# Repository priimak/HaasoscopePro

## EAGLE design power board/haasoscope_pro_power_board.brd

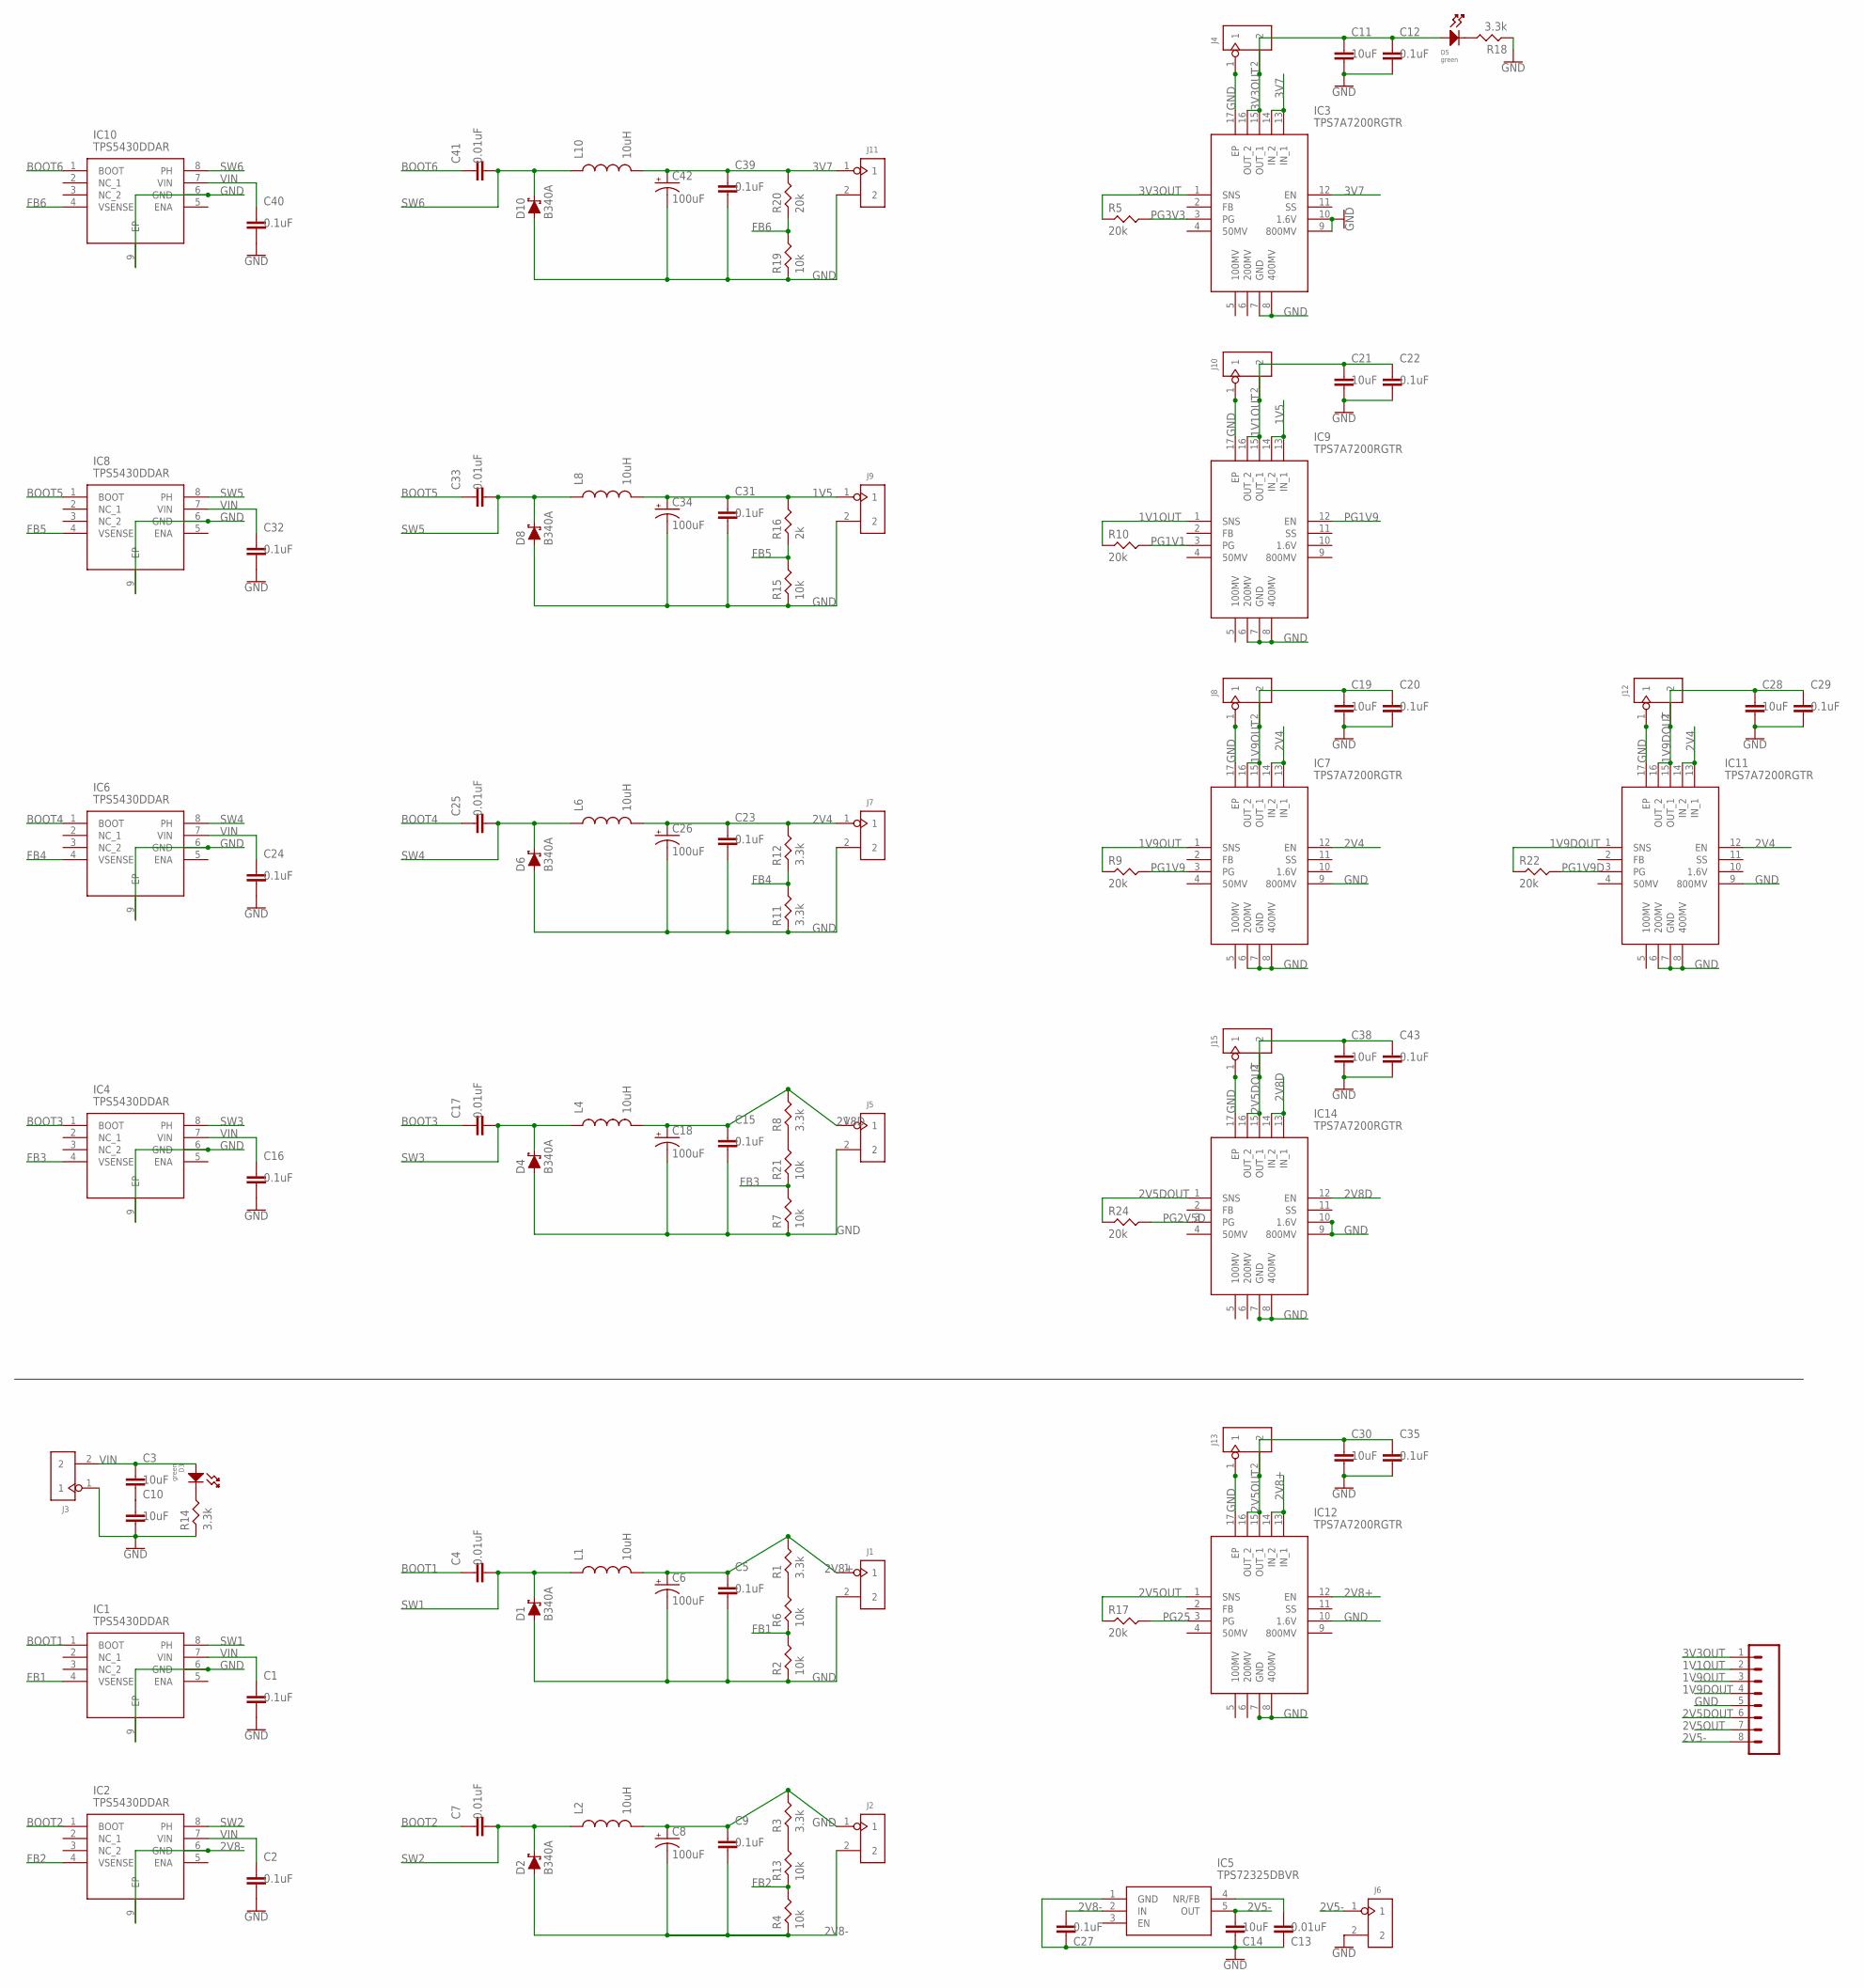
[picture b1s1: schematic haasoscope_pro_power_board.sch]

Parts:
C1, C2, C5, C9, C12, C15, C16, C20, C22, C23, C24, C27, C29, C31, C32, C35, C39, C40, C43: 0.1uF; RESC0402_N
C3, C10, C11, C14, C19, C21, C28, C30, C38: 10uF; RESC0805_N
C4, C7, C13, C17, C25, C33, C41: 0.01uF; RESC0402_N
C6, C8, C18, C26, C34, C42: 100uF; VISHAY_C; LCSC C7230
D1, D2, D4, D6, D8, D10: B340A; SMA-DIODE; LCSC C64982
D3, D5: green; LED0805
IC1, IC2, IC4, IC6, IC8, IC10: TPS5430DDAR; SOIC127P600X170-9N
IC3, IC7, IC9, IC11, IC12, IC14: TPS7A7200RGTR; QFN50P300X300X100-17N
IC5: TPS72325DBVR; SOT95P280X145-5N
J1, J2, J3, J4, J5, J6, J7, J8, J9, J10, J11, J12, J13, J15: 2p-2.54; H2-2.54
J16: 8pin; 1X08
L1, L2, L4, L6, L8, L10: 10uH; CDRH125; LCSC C339970
R1, R3, R8, R11, R12, R14, R18: 3.3k; RES-0402
R2, R4, R6, R7, R13, R15, R19, R21: 10k; RES-0402
R5, R9, R10, R17, R20, R22, R24: 20k; RES-0402
R16: 2k; RES-0402

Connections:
1V1OUT: C21.1, C22.1, IC9.1 (SNS), IC9.15 (OUT_1), IC9.16 (OUT_2), J10.2, J16.2, R10.P$1
1V5: C31.1, C34.+, IC9.13 (IN_1), IC9.14 (IN_2), J9.1, L8.2, R16.P$2
1V9DOUT: C28.1, C29.1, IC11.1 (SNS), IC11.15 (OUT_1), IC11.16 (OUT_2), J12.2, J16.4, R22.P$1
1V9OUT: C19.1, C20.1, IC7.1 (SNS), IC7.15 (OUT_1), IC7.16 (OUT_2), J8.2, J16.3, R9.P$1
2V4: C23.1, C26.+, IC7.12 (EN), IC7.13 (IN_1), IC7.14 (IN_2), IC11.12 (EN), IC11.13 (IN_1), IC11.14 (IN_2), J7.1, L6.2, R12.P$2
2V5-: C14.1, IC5.5 (OUT), J6.1, J16.8
2V5DOUT: C38.1, C43.1, IC14.1 (SNS), IC14.15 (OUT_1), IC14.16 (OUT_2), J15.2, J16.6, R24.P$1
2V5OUT: C30.1, C35.1, IC12.1 (SNS), IC12.15 (OUT_1), IC12.16 (OUT_2), J13.2, J16.7, R17.P$1
2V8+: C5.1, C6.+, IC12.12 (EN), IC12.13 (IN_1), IC12.14 (IN_2), J1.1, L1.2, R1.P$2
2V8-: C8.-, C9.2, C27.1, D2.A, IC2.6 (GND), IC2.9 (EP), IC5.2 (IN), J2.2, R4.P$1
2V8D: C15.1, C18.+, IC14.12 (EN), IC14.13 (IN_1), IC14.14 (IN_2), J5.1, L4.2, R8.P$2
3V3OUT: C11.1, C12.1, D5.ANODE, IC3.1 (SNS), IC3.15 (OUT_1), IC3.16 (OUT_2), J4.2, J16.1, R5.P$1
3V7: C39.1, C42.+, IC3.12 (EN), IC3.13 (IN_1), IC3.14 (IN_2), J11.1, L10.2, R20.P$2
BOOT1: C4.1, IC1.1 (BOOT)
BOOT2: C7.1, IC2.1 (BOOT)
BOOT3: C17.1, IC4.1 (BOOT)
BOOT4: C25.1, IC6.1 (BOOT)
BOOT5: C33.1, IC8.1 (BOOT)
BOOT6: C41.1, IC10.1 (BOOT)
FB1: IC1.4 (VSENSE), R2.P$2, R6.P$1
FB2: IC2.4 (VSENSE), R4.P$2, R13.P$1
FB3: IC4.4 (VSENSE), R7.P$2, R21.P$1
FB4: IC6.4 (VSENSE), R11.P$2, R12.P$1
FB5: IC8.4 (VSENSE), R15.P$2, R16.P$1
FB6: IC10.4 (VSENSE), R19.P$2, R20.P$1
GND: C1.2, C2.2, C5.2, C6.-, C8.+, C9.1, C10.2, C11.2, C12.2, C13.2, C14.2, C15.2, C16.2, C18.-, C19.2, C20.2, C21.2, C22.2, C23.2, C24.2, C26.-, C27.2, C28.2, C29.2, C30.2, C31.2, C32.2, C34.-, C35.2, C38.2, C39.2, C40.2, C42.-, C43.2, D1.A, D4.A, D6.A, D8.A, D10.A, IC1.6 (GND), IC1.9 (EP), IC3.7 (GND), IC3.8 (400MV), IC3.9 (800MV), IC3.10 (1.6V), IC3.17 (EP), IC4.6 (GND), IC4.9 (EP), IC5.1 (GND), IC6.6 (GND), IC6.9 (EP), IC7.6 (200MV), IC7.7 (GND), IC7.8 (400MV), IC7.9 (800MV), IC7.17 (EP), IC8.6 (GND), IC8.9 (EP), IC9.6 (200MV), IC9.7 (GND), IC9.8 (400MV), IC9.17 (EP), IC10.6 (GND), IC10.9 (EP), IC11.6 (200MV), IC11.7 (GND), IC11.8 (400MV), IC11.9 (800MV), IC11.17 (EP), IC12.7 (GND), IC12.8 (400MV), IC12.10 (1.6V), IC12.17 (EP), IC14.7 (GND), IC14.8 (400MV), IC14.9 (800MV), IC14.10 (1.6V), IC14.17 (EP), J1.2, J2.1, J3.1, J4.1, J5.2, J6.2, J7.2, J8.1, J9.2, J10.1, J11.2, J12.1, J13.1, J15.1, J16.5, L2.2, R2.P$1, R3.P$2, R7.P$1, R11.P$1, R14.P$1, R15.P$1, R18.P$1, R19.P$1; also elsewhere on the board
unnamed: R1.P$1, R6.P$2
unnamed: R3.P$1, R13.P$2
unnamed: C3.2, C10.1
unnamed: C13.1, IC5.4 (NR/FB)
unnamed: D3.CATHODE, R14.P$2
unnamed: D5.CATHODE, R18.P$2
unnamed: R8.P$1, R21.P$2
unnamed 33: IC3.5 (100MV); also elsewhere on the board
unnamed 34: IC9.5 (100MV); also elsewhere on the board
unnamed 35: IC7.5 (100MV); also elsewhere on the board
PG1V1: IC9.3 (PG), R10.P$2
PG1V9: IC7.3 (PG), IC9.12 (EN), R9.P$2
PG1V9D: IC11.3 (PG), R22.P$2
PG2V5D: IC14.3 (PG), R24.P$2
PG3V3: IC3.3 (PG), R5.P$2
PG25: IC12.3 (PG), R17.P$2
SW1: C4.2, D1.C, IC1.8 (PH), L1.1
SW2: C7.2, D2.C, IC2.8 (PH), L2.1
SW3: C17.2, D4.C, IC4.8 (PH), L4.1
SW4: C25.2, D6.C, IC6.8 (PH), L6.1
SW5: C33.2, D8.C, IC8.8 (PH), L8.1
SW6: C41.2, D10.C, IC10.8 (PH), L10.1
VIN: C1.1, C2.1, C3.1, C16.1, C24.1, C32.1, C40.1, D3.ANODE, IC1.7 (VIN), IC2.7 (VIN), IC4.7 (VIN), IC6.7 (VIN), IC8.7 (VIN), IC10.7 (VIN), J3.2; also elsewhere on the board

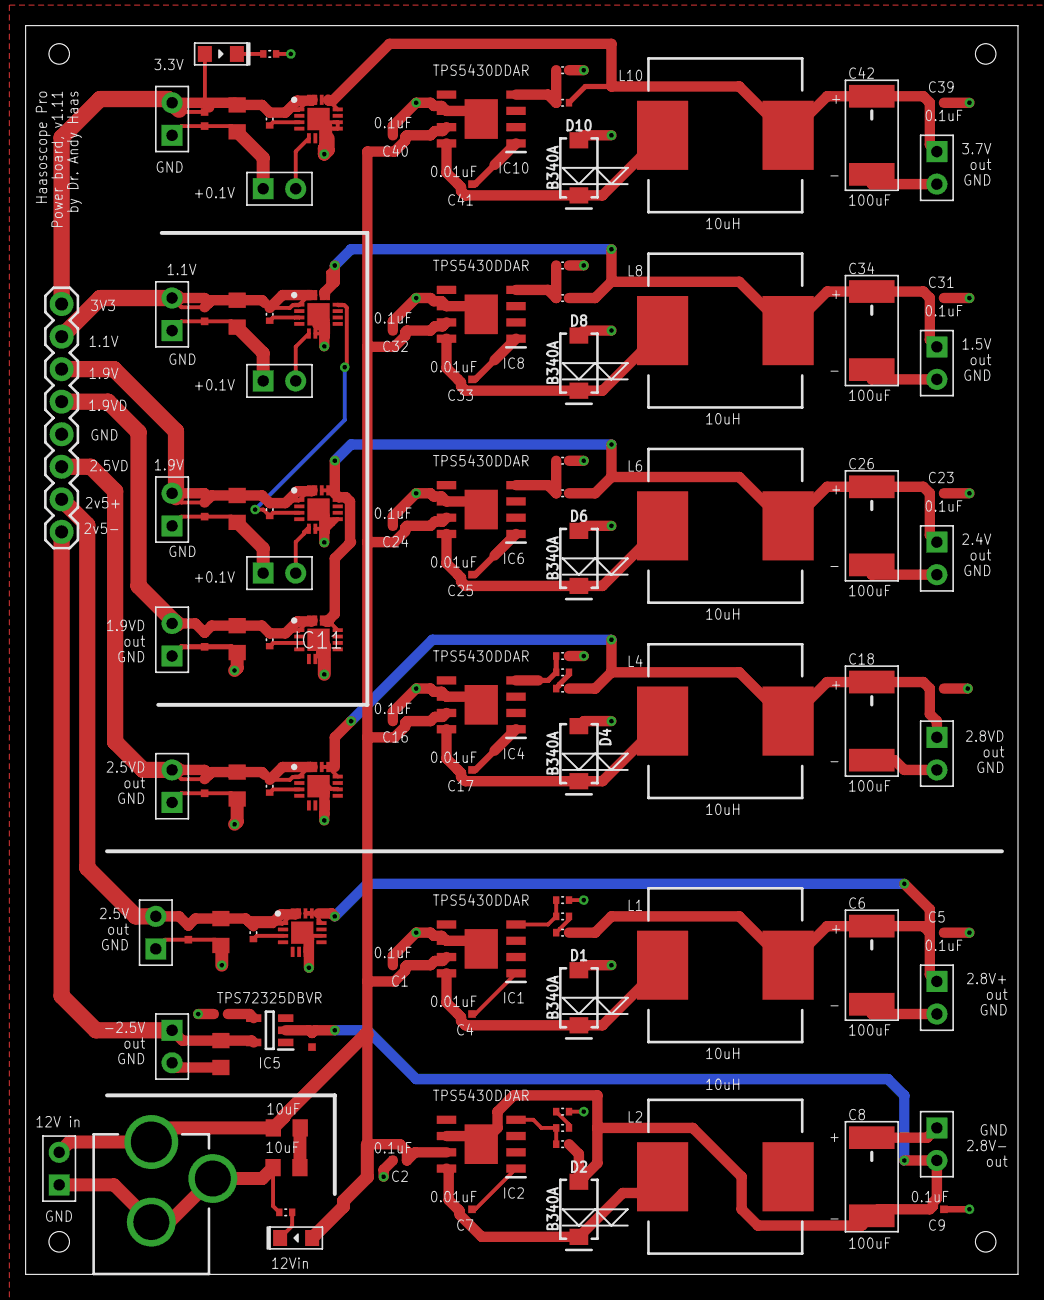
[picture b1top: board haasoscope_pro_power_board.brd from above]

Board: 2 copper layers, 77.5 x 97.5 mm, 110 parts (0 on the bottom side), 49 nets.

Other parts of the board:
CN1: 12Vin; DCJACK_2MM_PTH
J17, J18, J19: 2p-2.54; H2-2.54

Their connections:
GND: CN1.GND, CN1.GNDBREAK, J17.1, J18.1, J19.1; also elsewhere on the board
unnamed 33: J19.2; also elsewhere on the board
unnamed 34: J18.2; also elsewhere on the board
unnamed 35: J17.2; also elsewhere on the board
VIN: CN1.PWR; also elsewhere on the board

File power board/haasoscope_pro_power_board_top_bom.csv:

Comment,Designator,Footprint,LCSC Part #
0.1uF,C1 C2 C5 C9 C12 C15 C16 C20 C22 C23 C24 C27 C31 C32 C35 C39 C40,RESC0402_N,
0.01uF,C4 C7 C13 C17 C25 C33 C41,RESC0402_N,
1k,R8,RES-0402,
2k,R16,RES-0402,
3.3k,R1 R3 R11 R12 R14 R18,RES-0402,
10k,R2 R4 R6 R7 R13 R15 R19,RES-0402,
10uF,C3 C10 C11 C14 C19 C21 C30,RESC0805_N,
10uH,L1 L2 L4 L6 L8 L10,CDRH125,C339970
20k,R5 R9 R10 R17 R20,RES-0402,
100uF,C6 C8 C18 C26 C34 C42,VISHAY_C,C7230
B340A,D1 D2 D4 D6 D8 D10,SMA-DIODE,C64982
TPS7A7200RGTR,IC3 IC7 IC9 IC12,QFN50P300X300X100-17N,
TPS5430DDAR,IC1 IC2 IC4 IC6 IC8 IC10,SOIC127P600X170-9N,
TPS72325DBVR,IC5,SOT95P280X145-5N,
green,D3 D5,LED0805,

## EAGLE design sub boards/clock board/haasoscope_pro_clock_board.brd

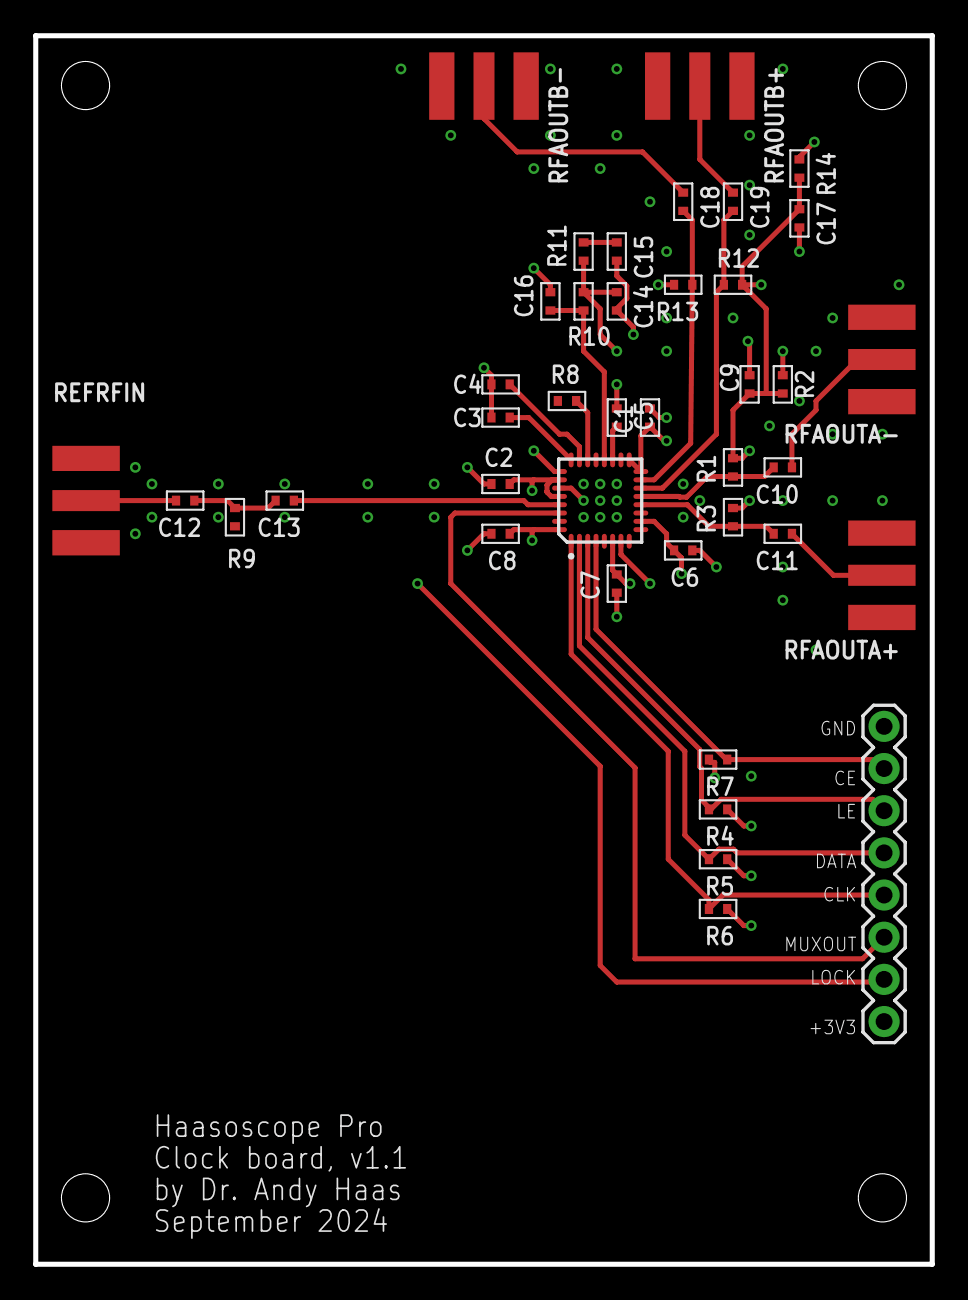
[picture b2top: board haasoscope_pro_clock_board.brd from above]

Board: 4 copper layers, 54.0 x 74.0 mm, 40 parts (0 on the bottom side), 27 nets.

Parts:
C1, C2, C3, C4, C5, C6, C7, C8, C9, C17: 0.1uF; C0402
C10, C11, C18, C19: 0.1nF; C0402
C12, C13: 1nF; C0402
C14: 2.7nF; C0402
C15: 47nF; C0402
C16: 680pF; C0402
J4: 8pin; 1X08
R1, R3, R9, R12, R13: 47; R0402
R2, R14: 0; R0402
R4, R5, R6, R7: 10k; R0402
R8: 5.1k; R0402
R10: 1k; R0402
R11: 360; R0402
REFRFIN: sma; SMA_EDGELAUNCH
RFAOUTA+: sma; SMA_EDGELAUNCH
RFAOUTA-: sma; SMA_EDGELAUNCH
RFAOUTB+: sma; SMA_EDGELAUNCH
RFAOUTB-: sma; SMA_EDGELAUNCH
U4: ADF4350BCPZ; QFN50P500X500X100-33V2N

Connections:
+3V3: C1.P$1, C2.P$2, C6.P$2, C7.P$2, C8.P$1, J4.8, R2.P$1, R7.P$2, R14.P$1, U4.6, U4.10, U4.16, U4.17, U4.26, U4.28, U4.32
ADFCE: J4.2, R7.P$1, U4.4
ADFCLK: J4.5, R6.P$2, U4.1
ADFDATA: J4.4, R5.P$2, U4.2
ADFLE: J4.3, R4.P$2, U4.3
CPOUT: C14.P$1, R10.P$2, R11.P$1, U4.7
GND: C1.P$2, C2.P$1, C3.P$2, C4.P$1, C5.P$1, C6.P$1, C7.P$1, C8.P$2, C9.P$2, C14.P$2, C15.P$2, C16.P$2, C17.P$2, J4.1, R4.P$1, R5.P$1, R6.P$1, R8.P$1, R9.P$1, REFRFIN.GND@1, REFRFIN.GND@2, REFRFIN.GND@3, REFRFIN.GND@4, RFAOUTA+.GND@1, RFAOUTA+.GND@2, RFAOUTA+.GND@3, RFAOUTA+.GND@4, RFAOUTA-.GND@1, RFAOUTA-.GND@2, RFAOUTA-.GND@3, RFAOUTA-.GND@4, RFAOUTB+.GND@1, RFAOUTB+.GND@2, RFAOUTB+.GND@3, RFAOUTB+.GND@4, RFAOUTB-.GND@1, RFAOUTB-.GND@2, RFAOUTB-.GND@3, RFAOUTB-.GND@4, U4.8, U4.9, U4.11, U4.18, U4.21, U4.27, U4.31, U4.PAD@1_1, U4.PAD@1_2, U4.PAD@1_3, U4.PAD@2_1, U4.PAD@2_2, U4.PAD@2_3, U4.PAD@3_1, U4.PAD@3_2, U4.PAD@3_3
LD: J4.7, U4.25
MUXOUT: J4.6, U4.30
unnamed: C12.P$2, REFRFIN.P
unnamed: C12.P$1, C13.P$2, R9.P$2
unnamed: C15.P$1, R11.P$2
unnamed: C5.P$2, U4.19
unnamed: C4.P$2, U4.23
unnamed: R8.P$2, U4.22
REF_CLK: C13.P$1, U4.29
RFOUTASMA_N: C10.P$1, RFAOUTA-.P
RFOUTASMA_P: C11.P$1, RFAOUTA+.P
RFOUTA_N: C10.P$2, R1.P$1, U4.13
RFOUTA_P: C11.P$2, R3.P$1, U4.12
RFOUTBSMA_N: C18.P$1, RFAOUTB-.P
RFOUTBSMA_P: C19.P$1, RFAOUTB+.P
RFOUTB_N: C18.P$2, R13.P$1, U4.15
RFOUTB_P: C19.P$2, R12.P$1, U4.14
VOUT: C9.P$1, C17.P$1, R1.P$2, R2.P$2, R3.P$2, R12.P$2, R13.P$2, R14.P$2
VREF: C3.P$1, U4.24
VTUNE: C16.P$1, R10.P$1, U4.20

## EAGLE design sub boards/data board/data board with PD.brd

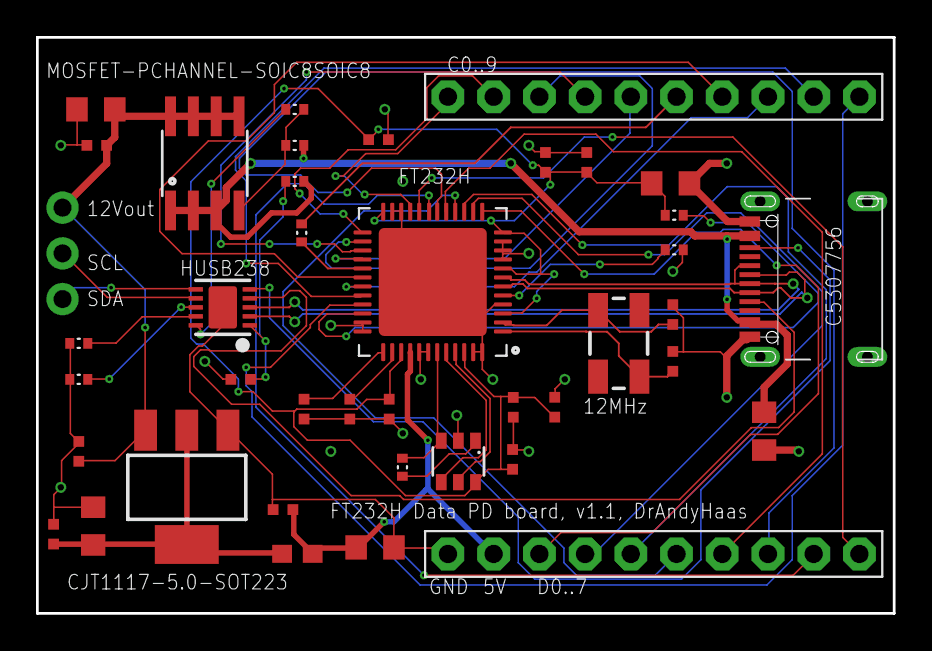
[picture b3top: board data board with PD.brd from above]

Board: 4 copper layers, 47.6 x 32.0 mm, 41 parts (0 on the bottom side), 46 nets.

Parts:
C1, C7, C13, C17, C19: 10uF; RESC0805_N
C2, C3, C4, C5, C6, C8, C9, C10, C11, C12, C18, C20, C21: 0.1uF; RESC0402_N
C14, C15: 16pF; RESC0402_N
C16: 1uF; RESC0402_N
FB1: 50mΩ 220Ω@100MHz 0603; 0603
IC1: 93LC56B; SOT23-6
IC2: FT232HQ; QFN48_8MM
JP3: 1X03_ROUND
R1, R2: 12k; RES-0402
R4: 2.2k; RES-0402
R6: 27; RES-0402
R7: 10; RES-0402
R8: 5.1k; RES-0402
R9: 49.9k; RES-0402
R10, R13: 10k; RES-0402
U1: CJT1117-5.0-SOT223; SOT-223
U9: MOSFET-PCHANNEL-SOIC8SOIC8; SO08
U$4, U$5: PINHD-1X10; 1X10-BIG
X3: HUSB238; DFN10_3X3MM
X6: USBC; USB_C_CUSB31-CFM2AX-01-X
Y1: 12MHz; CRYSTAL-SMD-5X3

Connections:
5V: C6.2, C13.2, FB1.2, IC2.40, U$4.2
5VD: C19.2, C20.2, FB1.1, U1.2, U1.TER
C0: IC2.21, U$5.1
C1: IC2.25, U$5.2
C2: IC2.26, U$5.3
C3: IC2.27, U$5.4
C4: IC2.28, U$5.5
C6: IC2.30, U$5.7
C7: IC2.31, U$5.8
C8: IC2.32, U$5.9
C9: IC2.33, U$5.10
CC1: X3.4, X6.A5
CC2: X3.5, X6.B5
D0: IC2.13, U$4.3
D1: IC2.14, U$4.4
D2: IC2.15, U$4.5
D3: IC2.16, U$4.6
D4: IC2.17, U$4.7
D5: IC2.18, U$4.8
D6: IC2.19, U$4.9
D7: IC2.20, U$4.10
D_N: IC2.7, X3.3, X6.A6, X6.B6
D_P: IC2.6, X3.2, X6.A7, X6.B7
GATE: R8.P$2, R9.P$1, U9.4
GND: C1.1, C2.1, C3.1, C4.1, C5.1, C6.1, C7.1, C8.1, C9.1, C10.1, C11.1, C12.1, C13.1, C14.2, C15.2, C16.1, C17.1, C18.1, C19.1, C20.1, C21.1, IC1.2, IC2.4, IC2.9, IC2.10, IC2.11, IC2.22, IC2.23, IC2.35, IC2.36, IC2.41, IC2.42, IC2.47, IC2.48, IC2.THERMAL, R2.P$1, R10.P$2, R13.P$2, U1.1, U$4.1, X3.GND, X6.A1B12, X6.B1A12
unnamed: IC2.5, R2.P$2
unnamed: C14.1, IC2.1, Y1.3
unnamed: C15.1, IC2.2, Y1.1
unnamed: IC2.29, R6.P$1
unnamed: R6.P$2, U$5.6
unnamed: C16.2, R7.P$1, X3.1
unnamed: IC2.34, R1.P$1
unnamed: R8.P$1, X3.10
unnamed: IC1.3, IC2.43, R4.P$2
unnamed: IC1.5, IC2.45
unnamed: IC1.4, IC2.44
unnamed: IC1.1, R4.P$1
unnamed: R13.P$1, X3.8
unnamed: R10.P$1, X3.9
SCL: JP3.2, X3.7
SDA: JP3.3, X3.6
VBUS: C7.2, R7.P$2, R9.P$2, U9.1, U9.2, U9.3, X6.A4B9, X6.B4A9
VCC1V8: C2.2, IC2.38
VCC3V3: C1.2, C3.2, C5.2, C8.2, C9.2, C10.2, C11.2, C12.2, IC1.6, IC2.3, IC2.8, IC2.12, IC2.24, IC2.39, IC2.46, R1.P$2
VCCA: C4.2, IC2.37
VOUT: C17.2, C18.2, C21.2, JP3.1, U1.3, U9.5, U9.6, U9.7, U9.8

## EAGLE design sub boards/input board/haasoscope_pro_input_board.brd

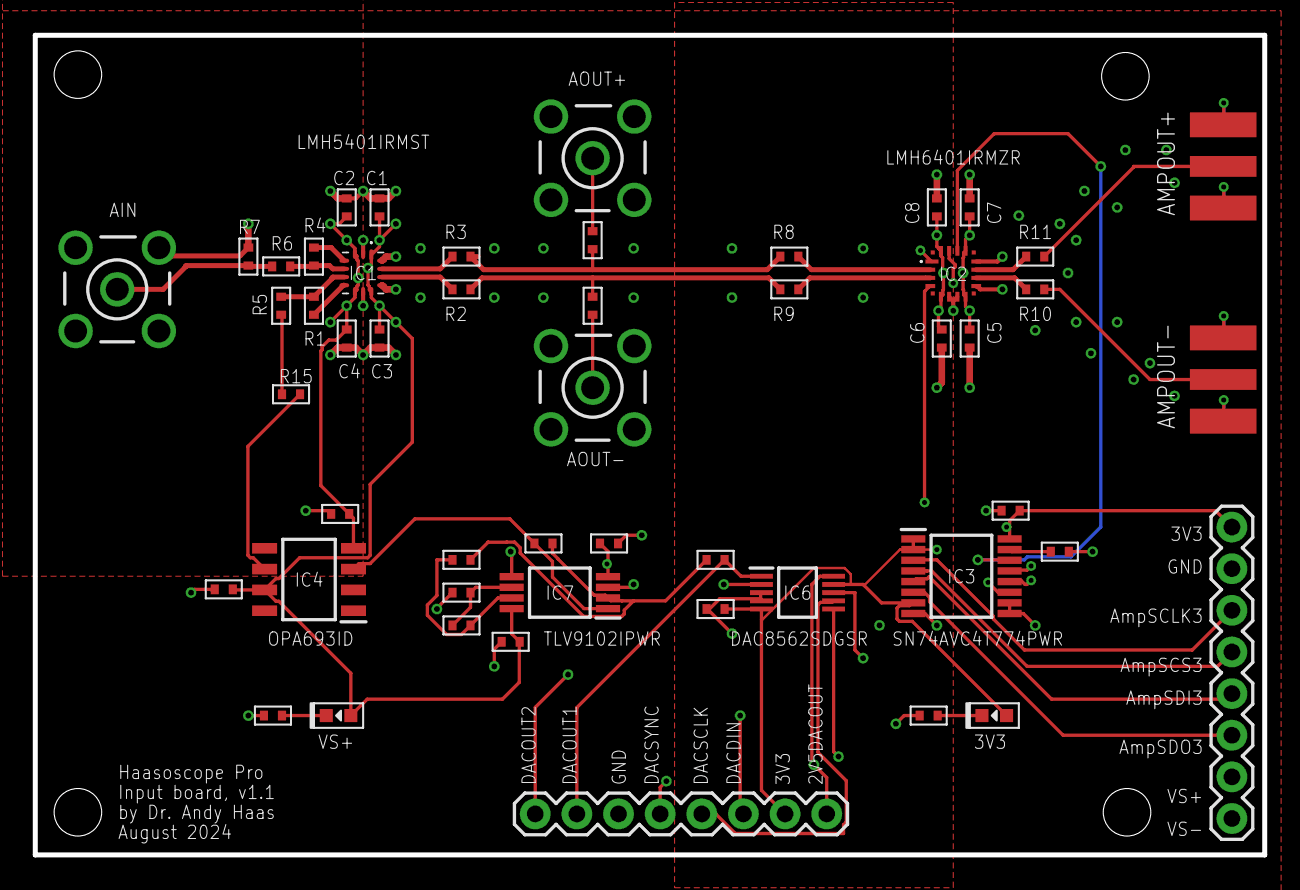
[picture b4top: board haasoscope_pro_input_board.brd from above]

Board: 4 copper layers, 75.0 x 50.0 mm, 51 parts (0 on the bottom side), 43 nets.

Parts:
AIN: BU-SMB-V
AMPOUT+: out+; SMA_EDGELAUNCH
AMPOUT-: out-; SMA_EDGELAUNCH
AOUT+: BU-SMB-V
AOUT-: BU-SMB-V
C1, C2, C3, C4, C5, C6, C7, C8, C9, C10, C11, C12, C13, C14, C15: 0.1uF; C0402
D1, D2: green; LED0603
IC1: LMH5401IRMST; LMH5401IRMSR
IC2: LMH6401IRMZR
IC3: SN74AVC4T774PWR; SOP65P640X120-16N
IC4: OPA693ID; SOIC127P600X175-8N
IC6: DAC8562SDGSR; SOP50P490X110-10N
IC7: TLV9102IPWR; SOP65P640X120-8N
J1, J4: 8pin; 1X08
R1, R4: 127; R0402
R2, R3, R10, R11: 39; R0402
R5: 66.5; R0402
R6: 22.6; R0402
R7: 357; R0402
R8, R9, R15, R21, R22: 0; R0402
R12, R13, R16, R18, R19, R20: 1k; R0402
R17: 2k; R0402

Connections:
1V25OUT-: IC7.7, R18.P$2, R20.P$2
2V5DACOUT: IC6.10, J1.8, R17.P$1
3V3: C10.P$1, C15.P$1, D2.ANODE, IC3.1, IC3.2, IC3.7, IC3.16, IC6.5, IC6.9, J1.7, J4.1
AIN: AIN.1, R6.P$1, R7.P$2
AIN_N: IC1.5, R4.P$1, R6.P$2
AIN_P: IC1.6, R1.P$1, R5.P$2
AMPIN_N: IC2.3, R9.P$2
AMPIN_P: IC2.2, R8.P$2
AMPOUTSMA_N: AMPOUT-.P, R10.P$2
AMPOUTSMA_P: AMPOUT+.P, R11.P$2
AMPOUT_N: IC2.10, R10.P$1
AMPOUT_P: IC2.11, R11.P$1
AMPSCLK: IC2.14, IC3.14
AMPSCS: IC2.15, IC3.13
AMPSDI: IC2.1, IC3.12
AMPSDO: IC2.4, IC3.11
AOFFSET: R5.P$1, R15.P$2
AOUTSMA_N: R2.P$2, R9.P$1, R22.P$1
AOUTSMA_P: R3.P$2, R8.P$1, R21.P$1
AOUT_N: IC1.12, R2.P$1
AOUT_P: IC1.13, R3.P$1
DACAMPOUT1: IC4.3, IC7.1, R19.P$1
DACDIN: IC6.8, J1.6
DACOUT1: IC6.1, J1.2, R16.P$2
DACOUT2: IC6.2, J1.1
DACSCLK: IC6.7, J1.5
DACSYNC: IC6.6, J1.4
GND: AIN.2, AIN.3, AIN.4, AIN.5, AMPOUT+.GND@1, AMPOUT+.GND@2, AMPOUT+.GND@3, AMPOUT+.GND@4, AMPOUT-.GND@1, AMPOUT-.GND@2, AMPOUT-.GND@3, AMPOUT-.GND@4, AOUT+.2, AOUT+.3, AOUT+.4, AOUT+.5, AOUT-.2, AOUT-.3, AOUT-.4, AOUT-.5, C1.P$2, C2.P$2, C3.P$2, C4.P$2, C5.P$2, C6.P$2, C7.P$2, C8.P$2, C9.P$2, C10.P$2, C11.P$2, C12.P$2, C13.P$2, C14.P$2, C15.P$2, IC1.2, IC1.9, IC1.11, IC1.14, IC2.6, IC2.7, IC2.9, IC2.12, IC3.8, IC3.9, IC3.10, IC6.3, IC6.4, IC7.3, IC7.5, J1.3, J4.2, R7.P$1, R12.P$1, R13.P$1
unnamed: D1.CATHODE, R12.P$2
unnamed: D2.CATHODE, R13.P$2
unnamed: IC7.2, R16.P$1, R19.P$2, R20.P$1
unnamed: AOUT-.1, R22.P$2
unnamed: IC7.6, R17.P$2, R18.P$1
unnamed: AOUT+.1, R21.P$2
unnamed: IC1.7, R1.P$2
unnamed: IC1.4, R4.P$2
OFFSETOUT: IC4.6, R15.P$1
SCLK3: IC3.3, J4.3
SCS3: IC3.4, J4.4
SDI3: IC3.5, J4.5
SDO3: IC3.6, J4.6
VS+: C1.P$1, C3.P$1, C5.P$1, C7.P$1, C9.P$1, C11.P$1, C13.P$1, D1.ANODE, IC1.1, IC1.10, IC2.8, IC2.13, IC3.15, IC4.7, IC7.8, J4.7
VS-: C2.P$1, C4.P$1, C6.P$1, C8.P$1, C12.P$1, C14.P$1, IC1.3, IC1.8, IC2.5, IC2.16, IC4.4, IC7.4, J4.8

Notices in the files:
parts and their libraries:
SparkFun-DiscreteSemi: Licensing: Creative Commons ShareAlike 4.0 International - https://creativecommons.org/licenses/by-sa/4.0
microbuilder: This work is placed in the public domain, and may be freely used for commercial and non-commercial work with the following conditions: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
